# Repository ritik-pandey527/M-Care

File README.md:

# M-Care: Revolutionizing Menstrual Hygiene and Waste Management

M-Care is a pioneering initiative focused on menstrual hygiene and sustainable sanitary waste management. This project combines smart technology, environmental sustainability, and community participation to address the pressing issue of sanitary waste disposal while promoting public health and environmental responsibility.

---

## Key Features

### 1. M-Care Bins
- **Convenient Disposal:** Strategically placed smart bins for hygienic and eco-friendly sanitary waste disposal.
- **Real-Time Monitoring:** Admin panel tracks the bin status to ensure timely maintenance and replacement.

### 2. M-Care Website
- **Bin Locator:** Easily locate the nearest M-Care bin.
- **Chatbot:** A friendly assistant to address menstruation-related queries.
- **Admin Panel:** Monitor bin usage and status in real time.

### 3. Upcycling Process
- **Waste to Resource:** Converts sanitary waste into valuable by-products like cellulose and eco-paper.
- **Steps Involved:**
  1. **Shredding:** Waste is shredded into smaller pieces.
  2. **Disinfection:** Ensures the waste is safe to handle.
  3. **Heating:** Aids in the breakdown of materials.
  4. **Chemical Treatment:** Extracts usable cellulose fibers.

---

## Website Overview

### Technologies Used
- **Frontend:** HTML, CSS, JavaScript
- **Backend:** Flask (Python)
- **Database:** SQLite
- **Mapping Tool:** Leaflet.js for interactive map integration

### Website Features
- **Homepage:** Highlights the mission and vision of M-Care.
- **About Us:** Educates users about the initiative and its impact.
- **Bin Locations:** Displays bin locations on an interactive map with real-time geolocation support.
- **Donate:** Links to support the initiative via donations.
- **Contact Us:** Provides contact details for inquiries and collaborations.

---

## How It Works

1. **Visit the Website:** Navigate to the M-Care homepage.
2. **Locate a Bin:** Use the interactive map to find the nearest bin.
3. **Dispose Waste Responsibly:** Deposit sanitary waste in M-Care bins.
4. **Upcycling Process:** Waste is transformed into eco-friendly products.
5. **Monitor Progress:** Admins ensure bins are maintained, and data is logged for sustainability metrics.

---

## Map Integration
The website features an interactive map powered by [Leaflet.js](https://leafletjs.com/), allowing users to:
- View the locations of M-Care bins.
- Automatically detect and display their current location.
- Search for locations manually for better navigation.

---

## Collaboration Opportunities
We welcome support from:
- **Donors:** Help us expand and sustain our operations.
- **Volunteers:** Join our movement to promote menstrual hygiene awareness.
- **Researchers and Innovators:** Enhance our upcycling technology.

---

## Future Goals
- **Expanded Reach:** Deploy more M-Care bins in urban and rural areas.
- **Enhanced Upcycling:** Develop advanced techniques for waste transformation.
- **Educational Campaigns:** Increase menstrual hygiene awareness globally.

---

## Acknowledgments
We thank our dedicated team, collaborators, and supporters for making M-Care a reality. Together, we can revolutionize menstrual hygiene and create a sustainable future.

Reseach Paper Link - https://ieeexplore.ieee.org/document/10520512

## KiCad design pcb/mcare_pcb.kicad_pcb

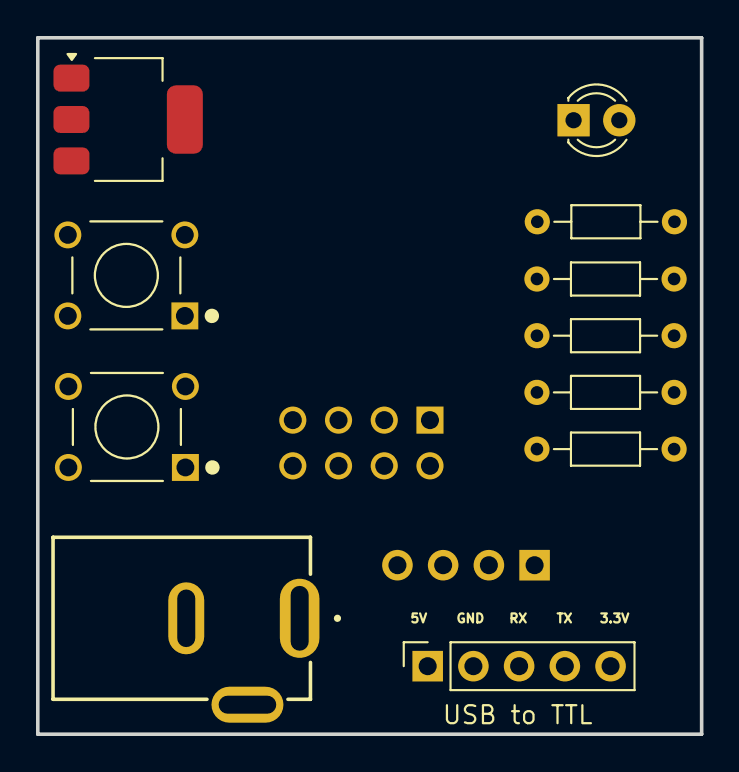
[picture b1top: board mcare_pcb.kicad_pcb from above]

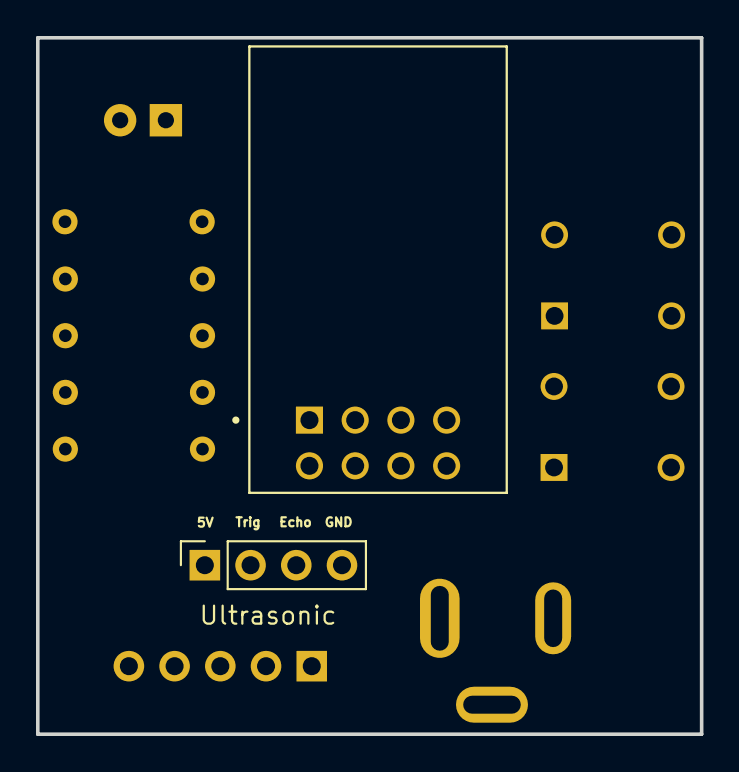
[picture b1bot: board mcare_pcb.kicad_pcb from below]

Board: 2 copper layers, 36.9 x 38.7 mm, 13 parts (2 on the bottom side), 10 nets, no tracks yet.

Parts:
D2: LED; LED_D3.0mm
J1: DCJ200-10-A-XX-K_REVA; GCT_DCJ200-10-A-XX-K_REVA
J3: Conn_01x04_Socket; PinSocket_1x04_P2.54mm_Vertical
J7: Conn_01x05_Socket; PinSocket_1x05_P2.54mm_Vertical
R2: 1K; R_Axial_DIN0204_L3.6mm_D1.6mm_P7.62mm_Horizontal
R3: 2K; R_Axial_DIN0204_L3.6mm_D1.6mm_P7.62mm_Horizontal
R7: 330; R_Axial_DIN0204_L3.6mm_D1.6mm_P7.62mm_Horizontal
R8, R9: 10K; R_Axial_DIN0204_L3.6mm_D1.6mm_P7.62mm_Horizontal
S3, S4: FSM8JH; SW_FSM8JH
U1: AMS1117; SOT-223-3_TabPin2
U2: ESP-01; MODULE_ESP-01

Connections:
3.3V: J7.5, R8.2, R9.2, U1.2 (VO), U2.5 (VCC)
5V: J1.1, J3.1, J7.1, U1.3 (VI)
Echo: J3.3, R7.1, U2.2 (GPIO2)
GND: D2.1 (K), J1.2, J1.3, J3.4, J7.2, R3.1, S3.3, S4.3, U1.1 (ADJ)
unnamed: D2.2 (A), R7.2
unnamed: R9.1, S4.1, U2.6 (~RST)
unnamed: R2.1, R3.2, U2.4 (RXD)
RX: J7.3, U2.8 (TXD)
TX: J7.4, R2.2
Trig: J3.2, R8.1, S3.1, U2.3 (GPIO0)

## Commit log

2024-12-16 final commit
2024-12-24 Create tp
